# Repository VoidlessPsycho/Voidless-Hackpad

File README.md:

# Voidless_Psycho's (me) Hackpad
Picture:\

Schematic:\

PCB:\

Case:\

BOM:\

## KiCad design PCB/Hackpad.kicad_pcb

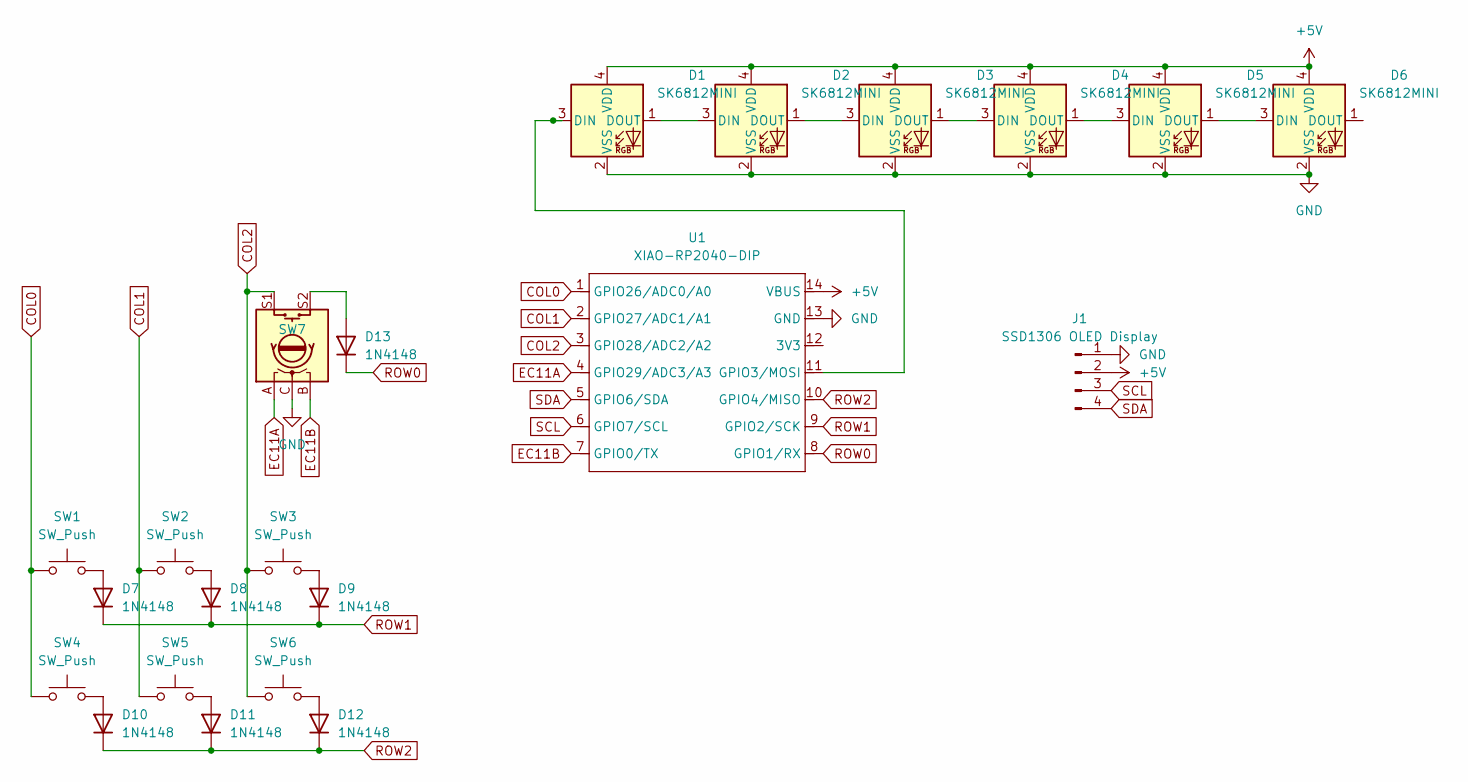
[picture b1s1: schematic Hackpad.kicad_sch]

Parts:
D1, D2, D3, D4, D5, D6: SK6812MINI; LED_6028R
D7, D8, D9, D10, D11, D12, D13: 1N4148; D_DO-35_SOD27_P7.62mm_Horizontal
J1: SSD1306 OLED Display; SSD1306-0.91-OLED-4pin-128x32
SW1, SW2, SW3, SW4, SW5, SW6: SW_Push; SW_Cherry_MX_1.00u_PCB
SW7: RotaryEncoder_Switch; RotaryEncoder_Alps_EC11E-Switch_Vertical_H20mm
U1: XIAO-RP2040-DIP

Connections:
+5V: D1.4 (VDD), D2.4 (VDD), D3.4 (VDD), D4.4 (VDD), D5.4 (VDD), D6.4 (VDD), J1.2, U1.14 (VBUS)
COL0: SW1.1, SW4.1, U1.1 (GPIO26/ADC0/A0)
COL1: SW2.1, SW5.1, U1.2 (GPIO27/ADC1/A1)
COL2: SW3.1, SW6.1, SW7.S1, U1.3 (GPIO28/ADC2/A2)
EC11A: SW7.A, U1.4 (GPIO29/ADC3/A3)
EC11B: SW7.B, U1.7 (GPIO0/TX)
GND: D1.2 (VSS), D2.2 (VSS), D3.2 (VSS), D4.2 (VSS), D5.2 (VSS), D6.2 (VSS), J1.1, SW7.C, U1.13 (GND)
unnamed: D1.3 (DIN), U1.11 (GPIO3/MOSI)
unnamed: D1.1 (DOUT), D2.3 (DIN)
unnamed: D2.1 (DOUT), D3.3 (DIN)
unnamed: D3.1 (DOUT), D4.3 (DIN)
unnamed: D4.1 (DOUT), D5.3 (DIN)
unnamed: D5.1 (DOUT), D6.3 (DIN)
unnamed: D7.2 (A), SW1.2
unnamed: D8.2 (A), SW2.2
unnamed: D9.2 (A), SW3.2
unnamed: D10.2 (A), SW4.2
unnamed: D11.2 (A), SW5.2
unnamed: D12.2 (A), SW6.2
unnamed: D13.2 (A), SW7.S2
ROW0: D13.1 (K), U1.8 (GPIO1/RX)
ROW1: D7.1 (K), D8.1 (K), D9.1 (K), U1.9 (GPIO2/SCK)
ROW2: D10.1 (K), D11.1 (K), D12.1 (K), U1.10 (GPIO4/MISO)
SCL: J1.3, U1.6 (GPIO7/SCL)
SDA: J1.4, U1.5 (GPIO6/SDA)

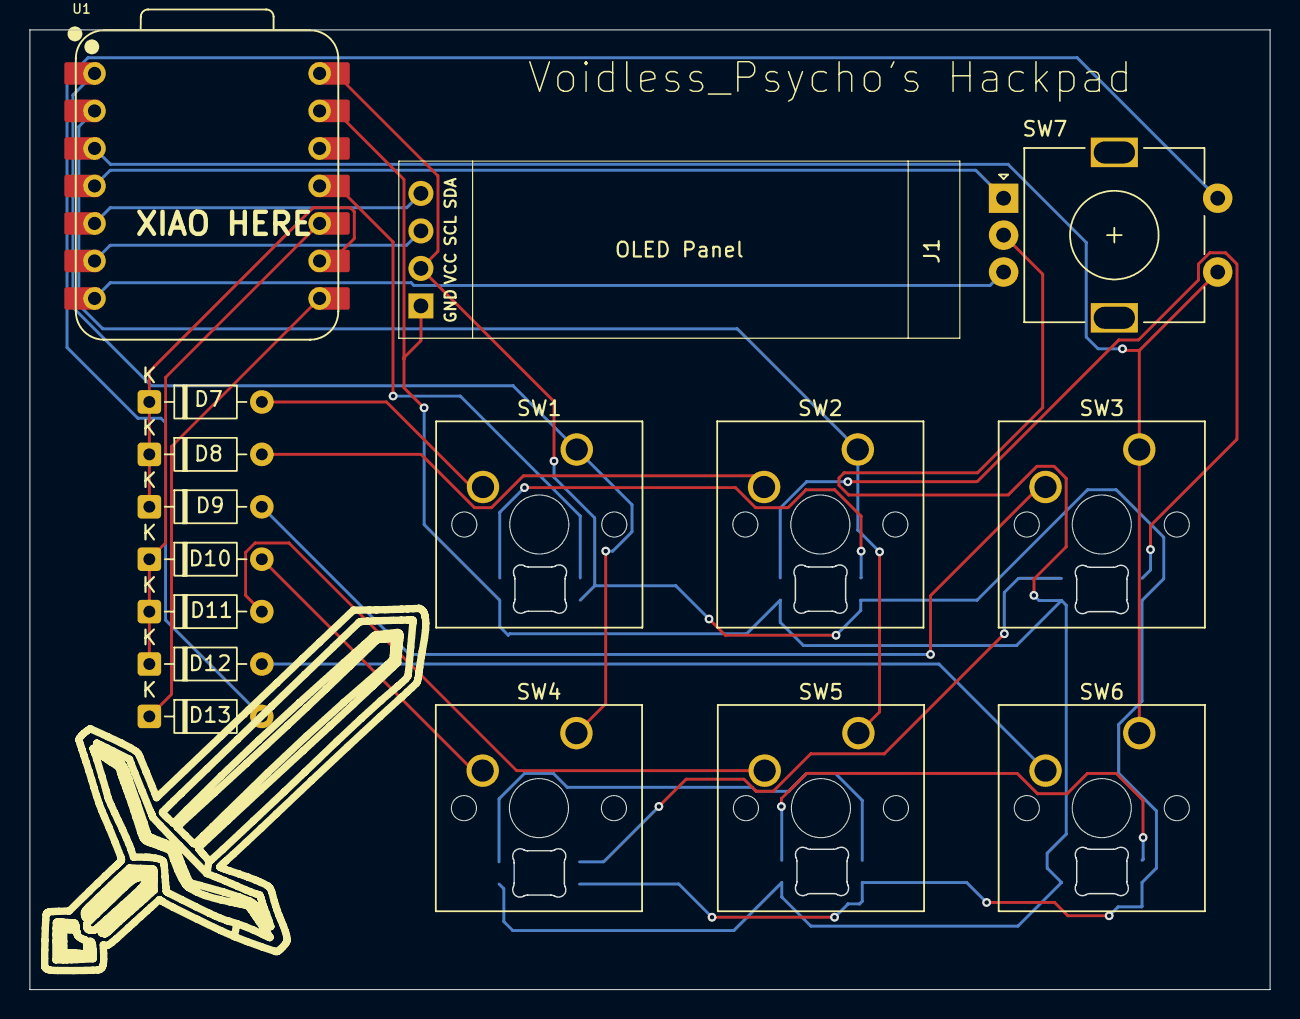
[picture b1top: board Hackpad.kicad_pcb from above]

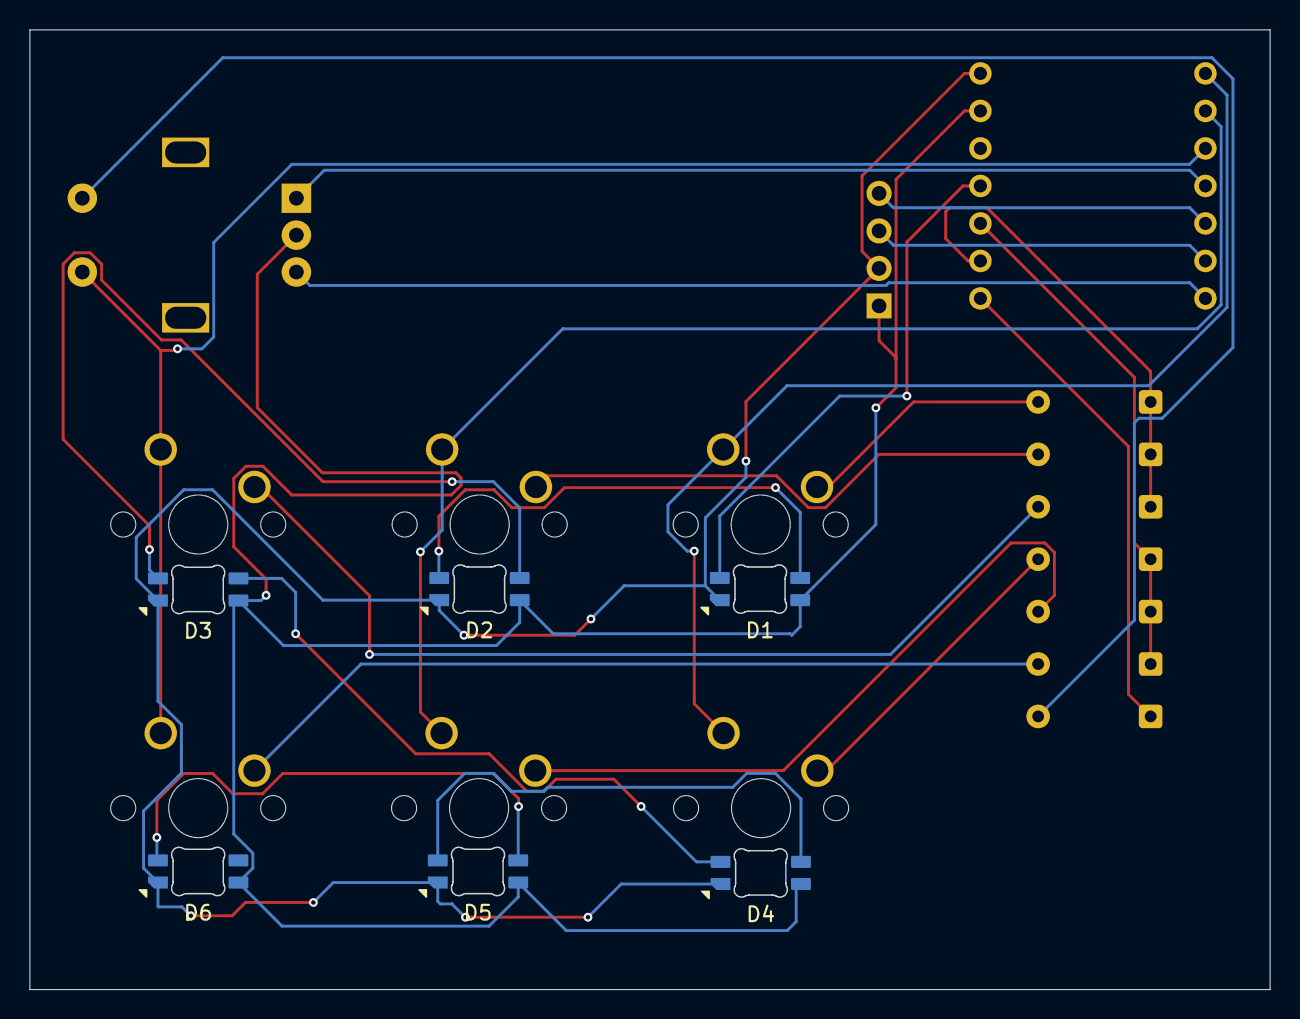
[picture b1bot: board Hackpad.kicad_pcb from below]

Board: 2 copper layers, 83.9 x 65.0 mm, 22 parts (6 on the bottom side), 25 nets.

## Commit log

2025-11-22 Added CIRCUITPY folder
2025-11-22 Added PCB Files from KiCAD
2025-11-22 Added Firmware Directory
2025-11-22 Added CAD Directory
2025-11-22 Added New CAD Directory
2025-11-23 Added BOM to README
2025-11-23 Refactor README structure and add BOM link
    Updated README to improve formatting and add BOM link.
2025-11-23 Fix formatting in README for BOM section
2025-11-23 Update README with BOM and item details
    Added BOM section with itemized list and links.
2025-11-23 Update README with new BOM details and image
    Added an image and updated BOM section with LED details.
2025-11-23 Update BOM section in README.md
    Removed detailed BOM list and replaced with an image.
2025-11-26 Gerber
